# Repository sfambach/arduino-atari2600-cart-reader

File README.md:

# Atari 2600 Cartridge Reader

Arduino firmware for dumping Atari 2600 cartridges, including bankswitched games.

Project page: https://www.fambach.net/ (Retro Projekt – Atari 2600 ROM einlesen)

## Boards

| Board | Address bus | Data bus |
|---|---|---|
| Arduino Mega 2560 | A0-A7 = PA0-PA7, A8-A12 = PC0-PC4 | D0-D7 = PL0-PL7 |
| Arduino Uno / Nano | 2 × 74HC595 on SPI (MOSI D11, SCK D13, latch A2): U1 = A0-A7, U2 = A8-A12 | D0-D7 = D2-D9 |
| Uno / Nano, MCP23017 boards | MCP23017 (I2C 0x20): GPA0-7 = A0-A7, GPB0-4 = A8-A12; `#define ADDR_MCP23017` in `hal.h` | D0-D7 = D2-D9 |

Cartridge slot: pin 23 = switched +5 V (BC327, LOW on D10 for Uno/Nano, D8 for Mega; sense on A0), pins 12 and 24 = GND. Read button on A1; reset button on the Arduino RESET line (Uno and Mega shields).

Boards (THT, KiCad) for Uno, Mega and Nano, plus MCP23017 variants for Uno and Nano: [`hardware/`](hardware/).

## Bankswitching

| Scheme | Size | Status |
|---|---|---|
| 2K, 4K | 2/4 KB | |
| F8, F6, F4 (+SC) | 8/16/32 KB | |
| E0 (Parker Bros.) | 8 KB | |
| E7 (M-Network) | 16 KB | |
| FA (CBS RAM+) | 12 KB | |
| FE (Activision) | 8 KB | experimental |
| 3F (Tigervision) | 8 KB+ (`D 3F <kb>`) | experimental |

Untested on hardware so far.

## Usage

Serial 115200 baud: `L` lists schemes, `D <scheme> [kb]` dumps, `P <hexaddr>` reads one byte, `S` prints the orientation and supply readings. The read button (A1) repeats the last `D` command (4K until one was given); `dump.py <port> listen <prefix>` saves those dumps. The cartridge is powered only during `D`, `P`, `S` and a button read, and only after the orientation check passed (experimental, see [`hardware/`](hardware/)).

```
pip install pyserial
python3 tools/dump.py /dev/ttyACM0 F8 game.bin
```

Test the dump with the emulator [Stella](https://stella-emu.github.io/).

## Credits

- [retrocartdumper](https://github.com/SvOlli/retrocartdumper) by Sven Oliver Moll (GPLv3)
- [Cart Reader](https://github.com/sanni/cartreader) by sanni (GPLv3)
- [vcsreaderfw](https://github.com/keoni29/vcsreaderfw) by Koen van Vliet (MIT)

## Authors

- **Stefan Fambach** (SteFam) – idea and concept, review and testing – https://www.fambach.net
- **Claude** (Anthropic AI) – implementation, via Claude Code

## AI disclosure

This project is built with AI assistance. Stefan Fambach had the idea, wrote the concept and reviews and tests every change; the implementation (schematics, PCB design files, firmware and documentation) is written largely by Claude (Anthropic) via Claude Code.

## License

GPLv3

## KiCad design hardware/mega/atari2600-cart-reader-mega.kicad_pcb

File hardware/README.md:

# Boards

Through-hole (THT) boards that carry the 24-pin cartridge slot. Pinout matches `AtariCartReader/hal.h`. Version 1.2.

| Variant | Board | Size | Notes |
|---|---|---|---|
| [`uno/`](uno/) | Arduino Uno R3 shield | 68.6 × 53.3 mm | address bus via 2 × 74HC595 (SPI) |
| [`mega/`](mega/) | Arduino Mega 2560 shield | 101.6 × 53.3 mm | direct port wiring (PA, PC, PL) |
| [`nano/`](nano/) | carrier for a plugged-in Arduino Nano | 80 × 62 mm | same circuit and firmware as the Uno, 2 × M3 holes |
| [`uno-mcp23017/`](uno-mcp23017/) | Uno shield, alternative | 68.6 × 53.3 mm | address bus via MCP23017 (I²C), firmware with `#define ADDR_MCP23017` in `hal.h` |
| [`nano-mcp23017/`](nano-mcp23017/) | Nano carrier, alternative | 80 × 62 mm | address bus via MCP23017 (I²C), firmware with `#define ADDR_MCP23017` |

Each folder: KiCad 7 project, schematic PDF, Gerber + drill ZIP, render, DRC report (0 errors, 0 unconnected; remaining warnings are silkscreen near the board edge and, on the shields, the modified shield footprint).

Changes in 1.2: Uno and Nano address bus via two 74HC595 on SPI (MOSI D11, SCK D13, latch A2) instead of the MCP23017, which costs about 1.75 € (Reichelt); the MCP23017 boards stay as `-mcp23017` variants. Read button (SW2, A1 to GND) on all boards, reset button (SW1, on the Arduino RESET line) on the Uno and Mega shields (the Nano's own reset button stays reachable), 6 × 6 mm tactile switches; Uno: C1 moved right to make room.

Changes in 1.1: switched cartridge supply with polyfuse and orientation check, mounting holes for the slot flanges (M2.5) as fixing points for the 3D-printed guide, ICSP header removed from the shields (firmware goes over USB), Uno: the mounting hole next to the ICSP header removed, Mega: slot moved to the middle of the board. Silkscreen: each part shows reference and value ("R4 10k"), "fambach.net" in the front title.

## Switched cartridge supply

[`switch/schalter.png`](switch/schalter.png): the cartridge is only powered while the firmware reads it. A BC327 (PNP) switches pin 23, a 200 mA polyfuse limits a short, and A0 measures the switched rail.

- Before switching on, the firmware checks the orientation with the supply off: a weak pull-up on data line D2 back-feeds the cartridge's VCC through the ROM's protection diode only if the cartridge sits the right way round. A reversed cartridge (or none) leaves A0 low and the supply stays off.
- All address lines are held low during the check, so a reversed cartridge's A12 (on slot pin 7 = A1) keeps the ROM disabled.
- The ADC thresholds are not confirmed on hardware yet; the `S` command prints both readings for calibration.

| Signal | Uno / Nano | Mega |
|---|---|---|
| Switch (LOW = on) | D10 | D8 |
| Sense (via 10 kΩ) | A0 | A0 |

## Wiring

| Cartridge pin | Signal | Uno shield / Nano board | Mega shield |
|---|---|---|---|
| 8 … 1 | A0 … A7 | U1 QA … QH (74HC595) | D22 … D29 (PA0 … PA7) |
| 22, 21, 19, 20, 18 | A8, A9, A10, A11, A12 | U2 QA … QE (74HC595) | D37 … D33 (PC0 … PC4) |
| 9, 10, 11, 13 … 17 | D0 … D7 | D2 … D9 | D49 … D42 (PL0 … PL7) |
| 23 | +5 V (switched) | BC327 collector | BC327 collector |
| 12, 24 | GND | GND | GND |

Uno / Nano: U1 SER = MOSI (D11), U1 QH' → U2 SER, SRCLK = SCK (D13), RCLK = latch (A2), OE to GND, SRCLR to +5 V; U2 QF–QH unused. The firmware shifts A8–A12 first, then A0–A7.

MCP23017 variants: MCP23017 at I2C 0x20 (A0–A2 to GND, RESET to +5 V), SDA = A4, SCL = A5 with 4k7 pull-ups; GPA0–7 = A0–A7, GPB0–4 = A8–A12.

## Bill of materials

| Ref | Part | Uno | Mega | Nano |
|---|---|---|---|---|
| J1 | Atari 2600 cartridge slot, 2 × 12, 2.54 mm | 1 | 1 | 1 |
| U1, U2 | 74HC595 (DIP-16) + DIP-16 socket | 2 | – | 2 |
| R3 | 1 kΩ, axial | 1 | 1 | 1 |
| R4, R5 | 10 kΩ, axial | 2 | 2 | 2 |
| R6 | 100 kΩ, axial | 1 | 1 | 1 |
| Q1 | BC327 (PNP, TO-92) | 1 | 1 | 1 |
| F1 | Polyfuse 200 mA radial, 5.08 mm (MF-R020, RXEF020) | 1 | 1 | 1 |
| C1, C2, C4 | 100 nF ceramic, 5 mm pitch | 3 | 1 (C2) | 3 |
| C3 | 10 µF electrolytic, 5 mm, 2 mm pitch | 1 | 1 | 1 |
| SW1, SW2 | Tactile switch 6 × 6 mm THT (SW1 reset, SW2 read) | 2 | 2 | 1 (SW2) |
| – | Stacking headers (Uno: 6, 8, 8, 10; Mega shield set) or 2 × 15 female headers (Nano) | 1 set | 1 set | 2 |
| – | M2.5 screws for the slot flanges / guide | 2 | 2 | 2 |

MCP23017 variants instead of U1/U2 and C4: U1 MCP23017-E/SP (DIP-28) + DIP-28 socket, R1/R2 4.7 kΩ axial, C1 100 nF.

## Assumptions

- **Slot row spacing 5.5 mm** centre to centre, pitch 2.54 mm, flange holes 45.5 mm apart. Footprint: `lib/atari.pretty`.
- **Guide base plate 61 × 17 mm** around the slot (dashed on F.Fab): no other parts there; `generator/plate.py` checks this on every build. The guide itself is not designed yet.
- The pin 13–24 row is the cartridge's label side (silkscreen "Etikettseite").
- Not built or tested yet.

## Cartridge orientation

[`pinout/pinout.png`](pinout/pinout.png) shows the cartridge contacts seen from below with the label up: pins 13–24 (D3 … +5V, GND) are on the label side, pins 1–12 (A7 … GND) on the back. Pin k sits opposite pin 25 − k, so a cartridge inserted the wrong way round puts +5V on D2. Sources: [WiringVCS](https://github.com/drzaiusx11/WiringVCS) and [The Hardware Book](https://isa.umh.es/temas/micros/doc/hwb/co_CartridgeAtari2600.html); quick check: pin 23 has continuity to the ROM's VCC pin.

## Cartridge slot drawing

[`slot-drawing/slot-masse.png`](slot-drawing/slot-masse.png) is a 2D dimension sketch of the 24-pin cartridge slot (top, front, side and bottom views), measured by hand; `zeichnung.py` regenerates it. It is the basis for the planned 3D-printed cartridge guide. A slot from another source may differ, so check these values first:

- Pins 2×12, pitch 2.54 mm, rows 5.5 mm apart (centre to centre).
- Overall length 51.3 mm, width 9 mm, height 16.1 mm above the board (6 mm lower part + 10.1 mm upper part).
- Lower part below the flanges: 35 mm long, 6 mm high, 7.4 mm wide.
- Body between the flanges 36.8 mm. Mounting flanges 7.2 mm long, 7.1 mm wide (across the pin rows), 6.5 mm high, with a Ø2.8 mm hole centred 2.9 mm from the outer edge.
- Flange underside flush with the top of the lower part (6 mm above the board), flange top at 12.5 mm. That leaves 3.6 mm to the slot top (confirmed).
- Card slot opening: 33.3 mm long, 2.2 mm wide; the spring contacts close to about 1.4 mm (estimated), which suits a 1.6 mm cartridge PCB. Slot depth 9 mm.

The measured slot sat on round-pin socket strips for extra height. They are not needed and are left out; the guide sets the cartridge height instead.

## Rebuild

Needs KiCad 7 (pcbnew Python), `xvfb-run`, Java and [Freerouting 1.9.0](https://github.com/freerouting/freerouting) at `/opt/tools/freerouting.jar` (or `FREEROUTING=`).

```
sh generator/build.sh uno|mega|nano     # schematic, board, routing, DRC, guide-plate check
sh generator/outputs.sh uno|mega|nano   # Gerber ZIP, schematic PDF, render
```

`generator/boards.py` holds netlist and placement.

## Credits

Arduino shield symbols and footprints: [arduino-kicad-library](https://github.com/Alarm-Siren/arduino-kicad-library) by Alarm-Siren, CC BY-SA 4.0 (`lib/LICENSE-arduino-library.txt`).

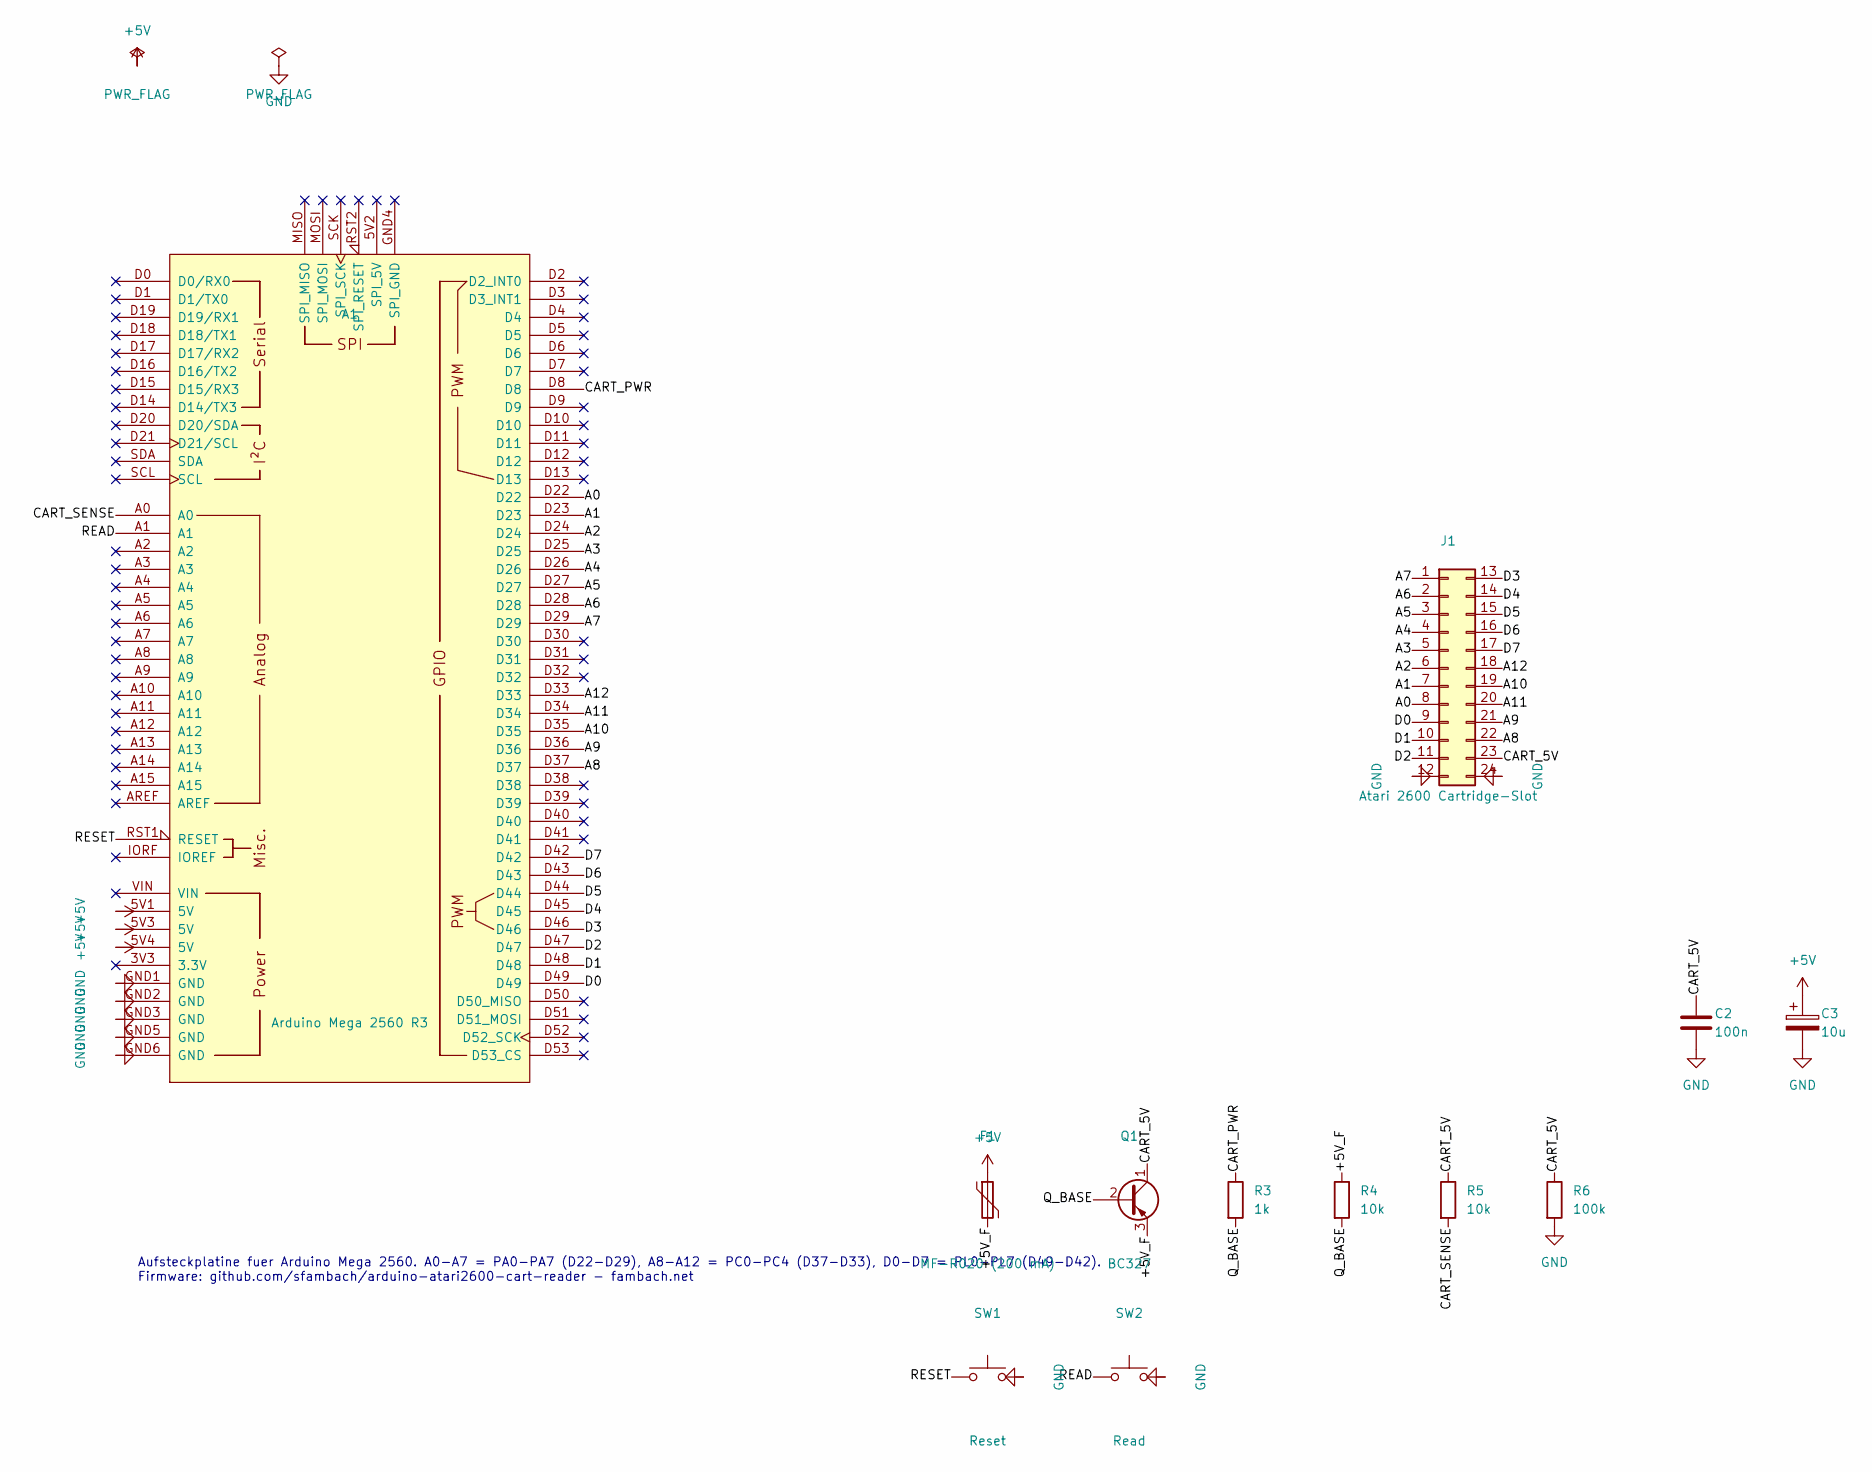
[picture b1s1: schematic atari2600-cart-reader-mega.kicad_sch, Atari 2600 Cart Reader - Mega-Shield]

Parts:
A1: Arduino Mega 2560 R3; Arduino_Mega2560_R3_Shield
C2: 100n; C_Disc_D5.0mm_W2.5mm_P5.00mm
C3: 10u; CP_Radial_D5.0mm_P2.00mm
F1: MF-R020 (200 mA); Fuse_PTC_Radial_P5.08mm
J1: Atari 2600 Cartridge-Slot; Atari2600_Cart_Slot_2x12_P2.54mm_Row5.50mm_Guide
Q1: BC327; TO-92_Inline
R3: 1k; R_Axial_DIN0207_L6.3mm_D2.5mm_P7.62mm_Horizontal
R4, R5: 10k; R_Axial_DIN0207_L6.3mm_D2.5mm_P7.62mm_Horizontal
R6: 100k; R_Axial_DIN0207_L6.3mm_D2.5mm_P7.62mm_Horizontal
SW1: Reset; SW_PUSH_6mm
SW2: Read; SW_PUSH_6mm

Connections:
+5V: A1.5V1 (5V), A1.5V3 (5V), A1.5V4 (5V), C3.1, F1.1
/+5V_F: F1.2, Q1.3 (E), R4.1
/A0: A1.D22, J1.8
/A1: A1.D23, J1.7
/A2: A1.D24, J1.6
/A3: A1.D25, J1.5
/A4: A1.D26, J1.4
/A5: A1.D27, J1.3
/A6: A1.D28, J1.2
/A7: A1.D29, J1.1
/A8: A1.D37, J1.22
/A9: A1.D36, J1.21
/A10: A1.D35, J1.19
/A11: A1.D34, J1.20
/A12: A1.D33, J1.18
/CART_5V: C2.1, J1.23, Q1.1 (C), R5.1, R6.1
/CART_PWR: A1.D8, R3.1
/CART_SENSE: A1.A0, R5.2
/D0: A1.D49, J1.9
/D1: A1.D48, J1.10
/D2: A1.D47, J1.11
/D3: A1.D46, J1.13
/D4: A1.D45, J1.14
/D5: A1.D44, J1.15
/D6: A1.D43, J1.16
/D7: A1.D42, J1.17
/Q_BASE: Q1.2 (B), R3.2, R4.2
/READ: A1.A1, SW2.1
/RESET: A1.RST1 (RESET), SW1.1
GND: A1.GND1 (GND), A1.GND2 (GND), A1.GND3 (GND), A1.GND5 (GND), A1.GND6 (GND), C2.2, C3.2, J1.12, J1.24, R6.2, SW1.2, SW2.2

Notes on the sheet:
Aufsteckplatine fuer Arduino Mega 2560. A0-A7 = PA0-PA7 (D22-D29), A8-A12 = PC0-PC4 (D37-D33), D0-D7 = PL0-PL7 (D49-D42). Firmware: github.com/sfambach/arduino-atari2600-cart-reader - fambach.net

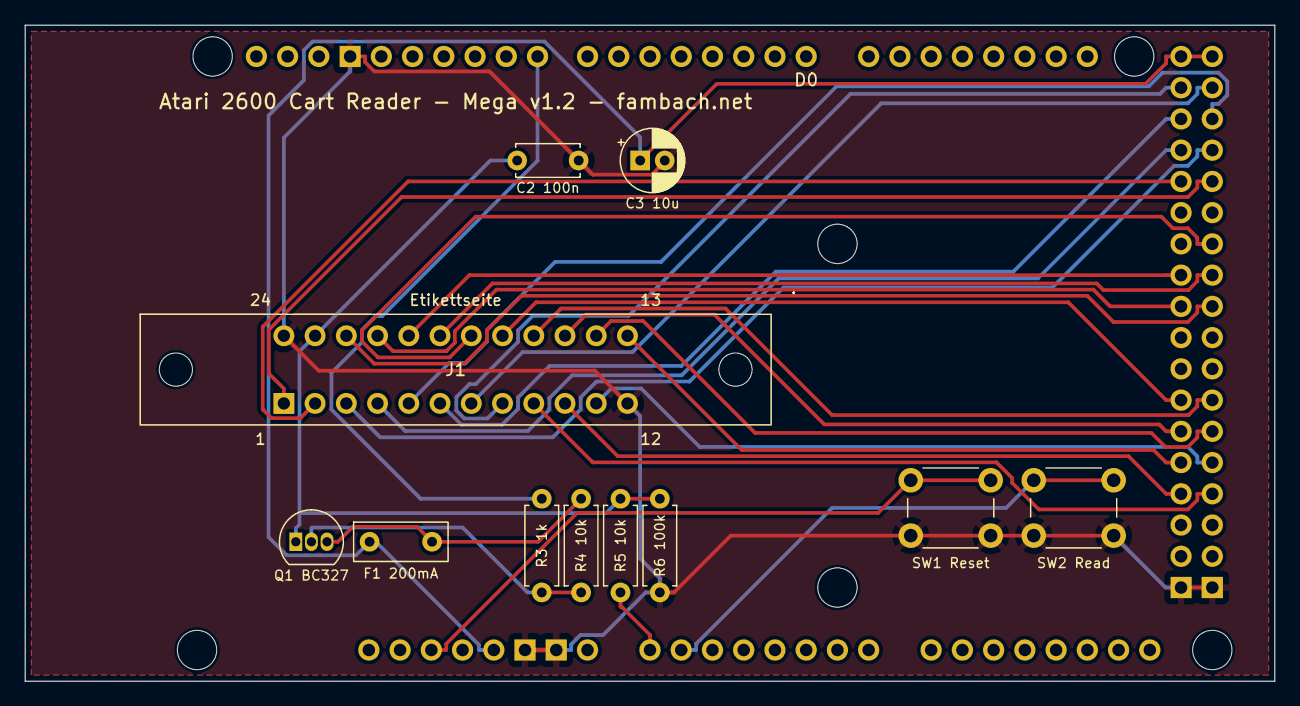
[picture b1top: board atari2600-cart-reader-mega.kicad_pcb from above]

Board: 2 copper layers, 101.6 x 53.3 mm, 12 parts (0 on the bottom side), 30 nets.

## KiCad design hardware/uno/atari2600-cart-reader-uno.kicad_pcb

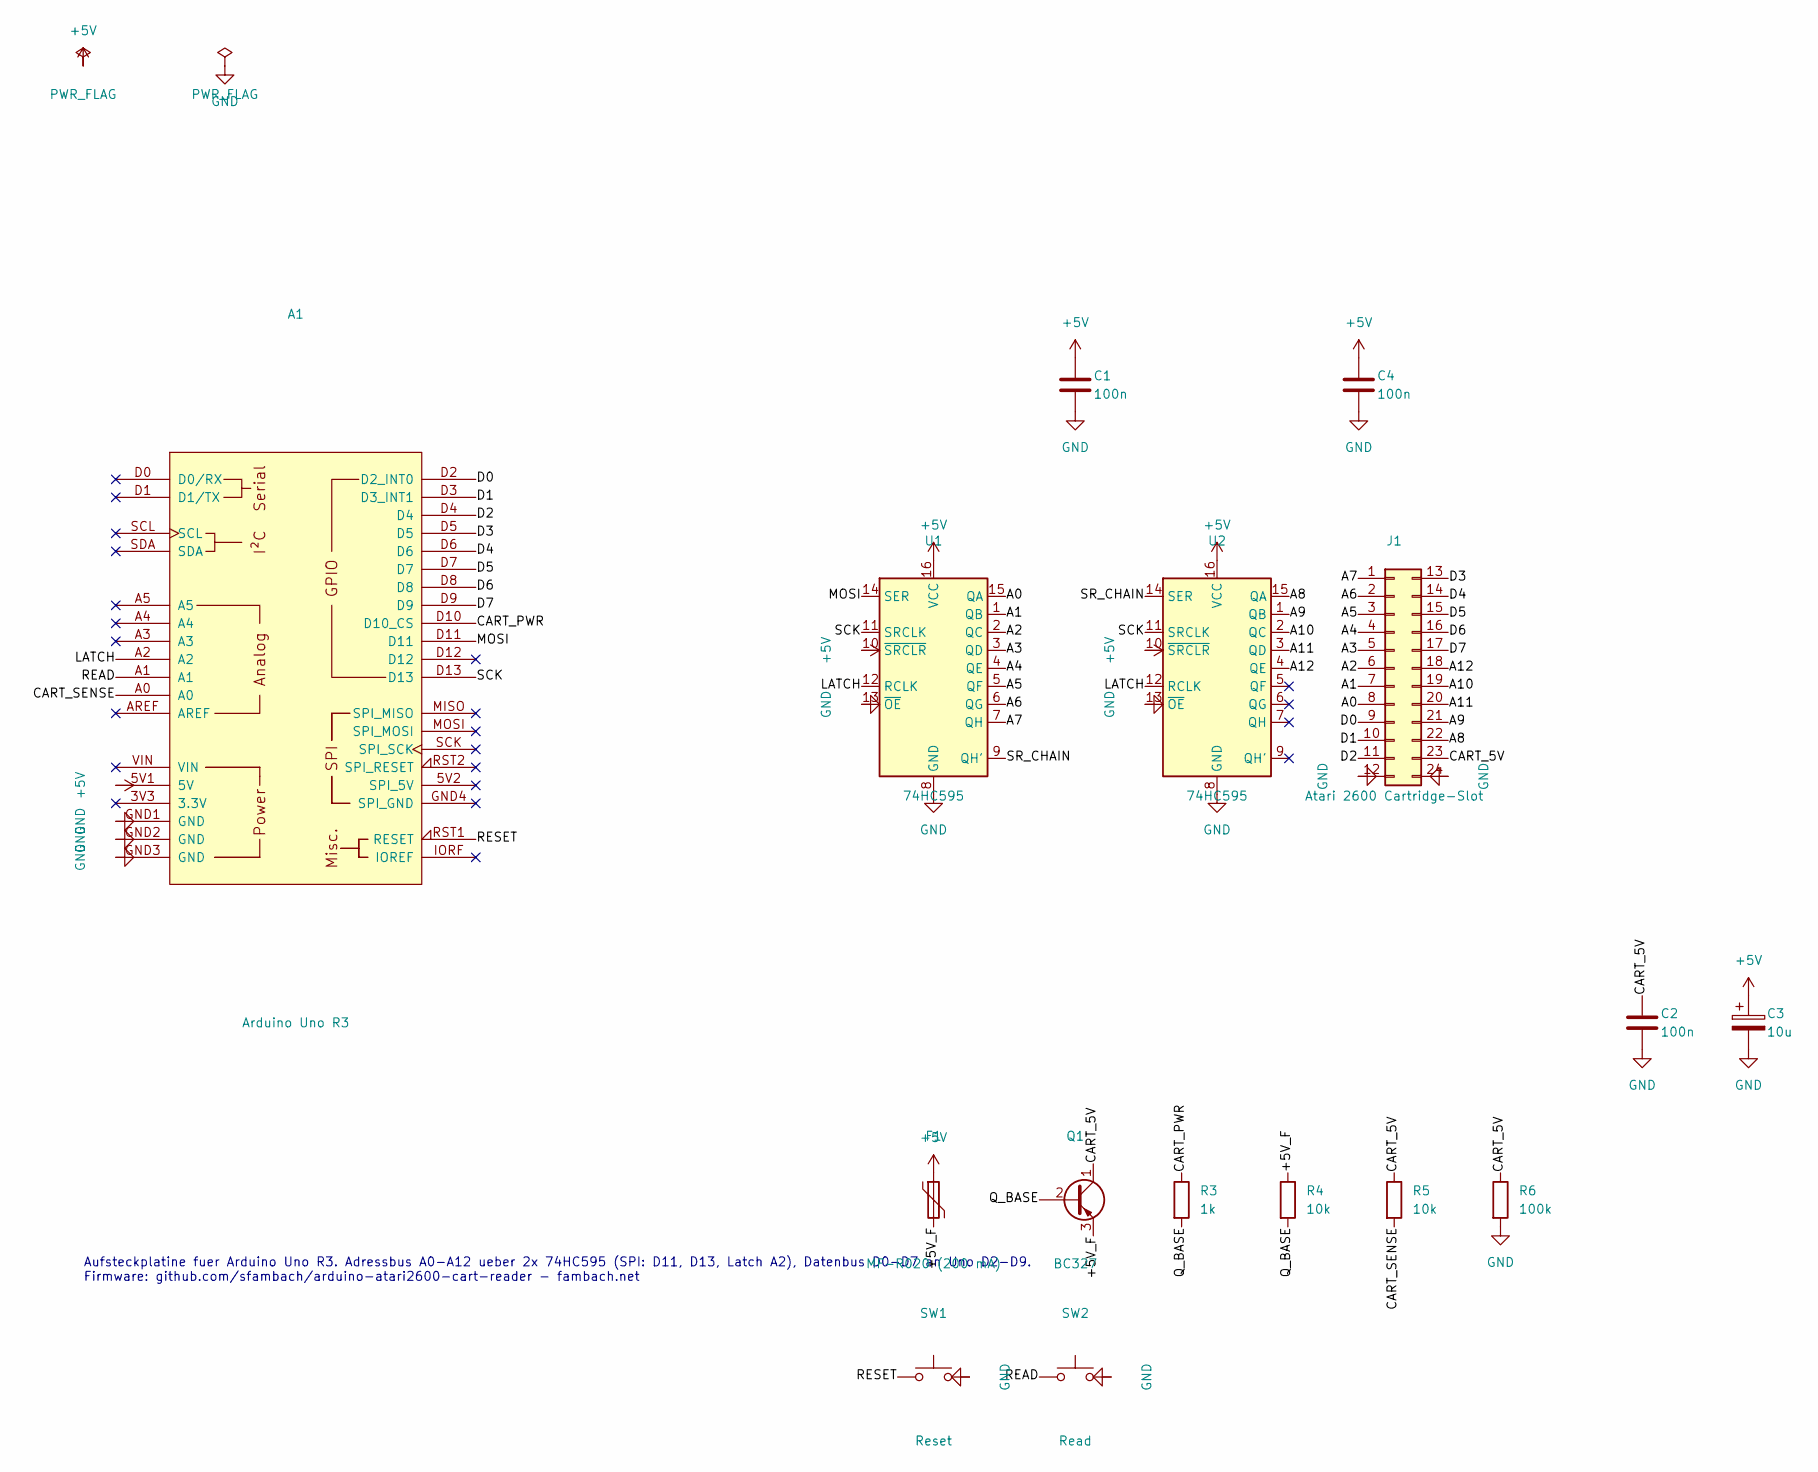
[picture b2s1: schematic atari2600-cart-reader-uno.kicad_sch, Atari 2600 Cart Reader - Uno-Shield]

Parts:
A1: Arduino Uno R3; Arduino_Uno_R3_Shield
C1, C2, C4: 100n; C_Disc_D5.0mm_W2.5mm_P5.00mm
C3: 10u; CP_Radial_D5.0mm_P2.00mm
F1: MF-R020 (200 mA); Fuse_PTC_Radial_P5.08mm
J1: Atari 2600 Cartridge-Slot; Atari2600_Cart_Slot_2x12_P2.54mm_Row5.50mm_Guide
Q1: BC327; TO-92_Inline
R3: 1k; R_Axial_DIN0207_L6.3mm_D2.5mm_P7.62mm_Horizontal
R4, R5: 10k; R_Axial_DIN0207_L6.3mm_D2.5mm_P7.62mm_Horizontal
R6: 100k; R_Axial_DIN0207_L6.3mm_D2.5mm_P7.62mm_Horizontal
SW1: Reset; SW_PUSH_6mm
SW2: Read; SW_PUSH_6mm
U1, U2: 74HC595; DIP-16_W7.62mm_Socket

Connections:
+5V: A1.5V1 (5V), C1.1, C3.1, C4.1, F1.1, U1.10 (~SRCLR), U1.16 (VCC), U2.10 (~SRCLR), U2.16 (VCC)
/+5V_F: F1.2, Q1.3 (E), R4.1
/A0: J1.8, U1.15 (QA)
/A1: J1.7, U1.1 (QB)
/A2: J1.6, U1.2 (QC)
/A3: J1.5, U1.3 (QD)
/A4: J1.4, U1.4 (QE)
/A5: J1.3, U1.5 (QF)
/A6: J1.2, U1.6 (QG)
/A7: J1.1, U1.7 (QH)
/A8: J1.22, U2.15 (QA)
/A9: J1.21, U2.1 (QB)
/A10: J1.19, U2.2 (QC)
/A11: J1.20, U2.3 (QD)
/A12: J1.18, U2.4 (QE)
/CART_5V: C2.1, J1.23, Q1.1 (C), R5.1, R6.1
/CART_PWR: A1.D10 (D10_CS), R3.1
/CART_SENSE: A1.A0, R5.2
/D0: A1.D2 (D2_INT0), J1.9
/D1: A1.D3 (D3_INT1), J1.10
/D2: A1.D4, J1.11
/D3: A1.D5, J1.13
/D4: A1.D6, J1.14
/D5: A1.D7, J1.15
/D6: A1.D8, J1.16
/D7: A1.D9, J1.17
/LATCH: A1.A2, U1.12 (RCLK), U2.12 (RCLK)
/MOSI: A1.D11, U1.14 (SER)
/Q_BASE: Q1.2 (B), R3.2, R4.2
/READ: A1.A1, SW2.1
/RESET: A1.RST1 (RESET), SW1.1
/SCK: A1.D13, U1.11 (SRCLK), U2.11 (SRCLK)
/SR_CHAIN: U1.9 (QH'), U2.14 (SER)
GND: A1.GND1 (GND), A1.GND2 (GND), A1.GND3 (GND), C1.2, C2.2, C3.2, C4.2, J1.12, J1.24, R6.2, SW1.2, SW2.2, U1.8 (GND), U1.13 (~OE), U2.8 (GND), U2.13 (~OE)

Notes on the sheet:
Aufsteckplatine fuer Arduino Uno R3. Adressbus A0-A12 ueber 2x 74HC595 (SPI: D11, D13, Latch A2), Datenbus D0-D7 an Uno D2-D9. Firmware: github.com/sfambach/arduino-atari2600-cart-reader - fambach.net

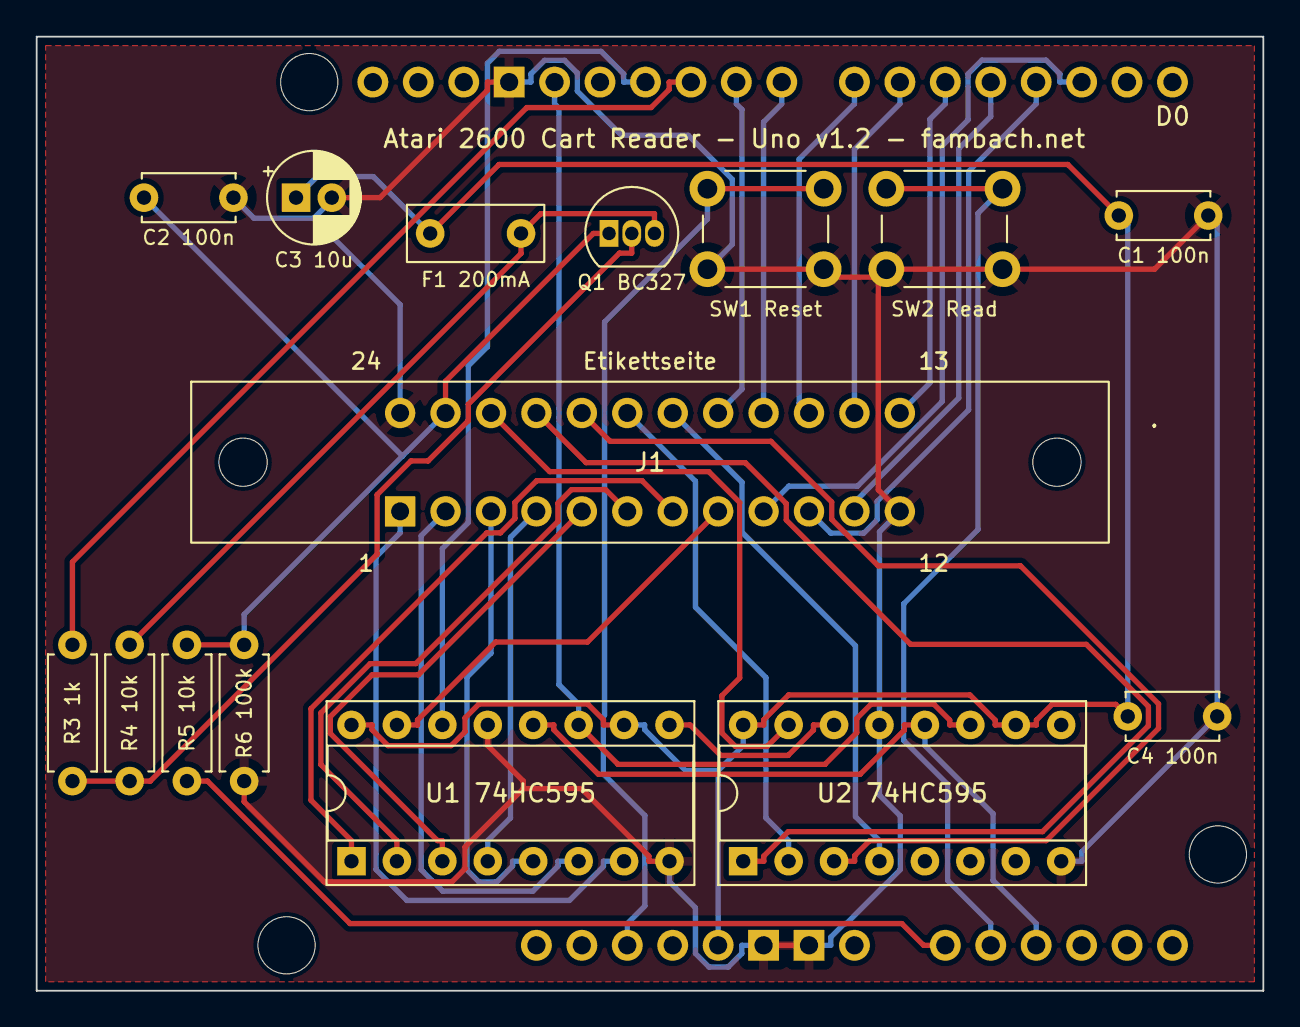
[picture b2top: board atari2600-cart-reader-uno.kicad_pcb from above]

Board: 2 copper layers, 68.6 x 53.3 mm, 16 parts (0 on the bottom side), 34 nets.

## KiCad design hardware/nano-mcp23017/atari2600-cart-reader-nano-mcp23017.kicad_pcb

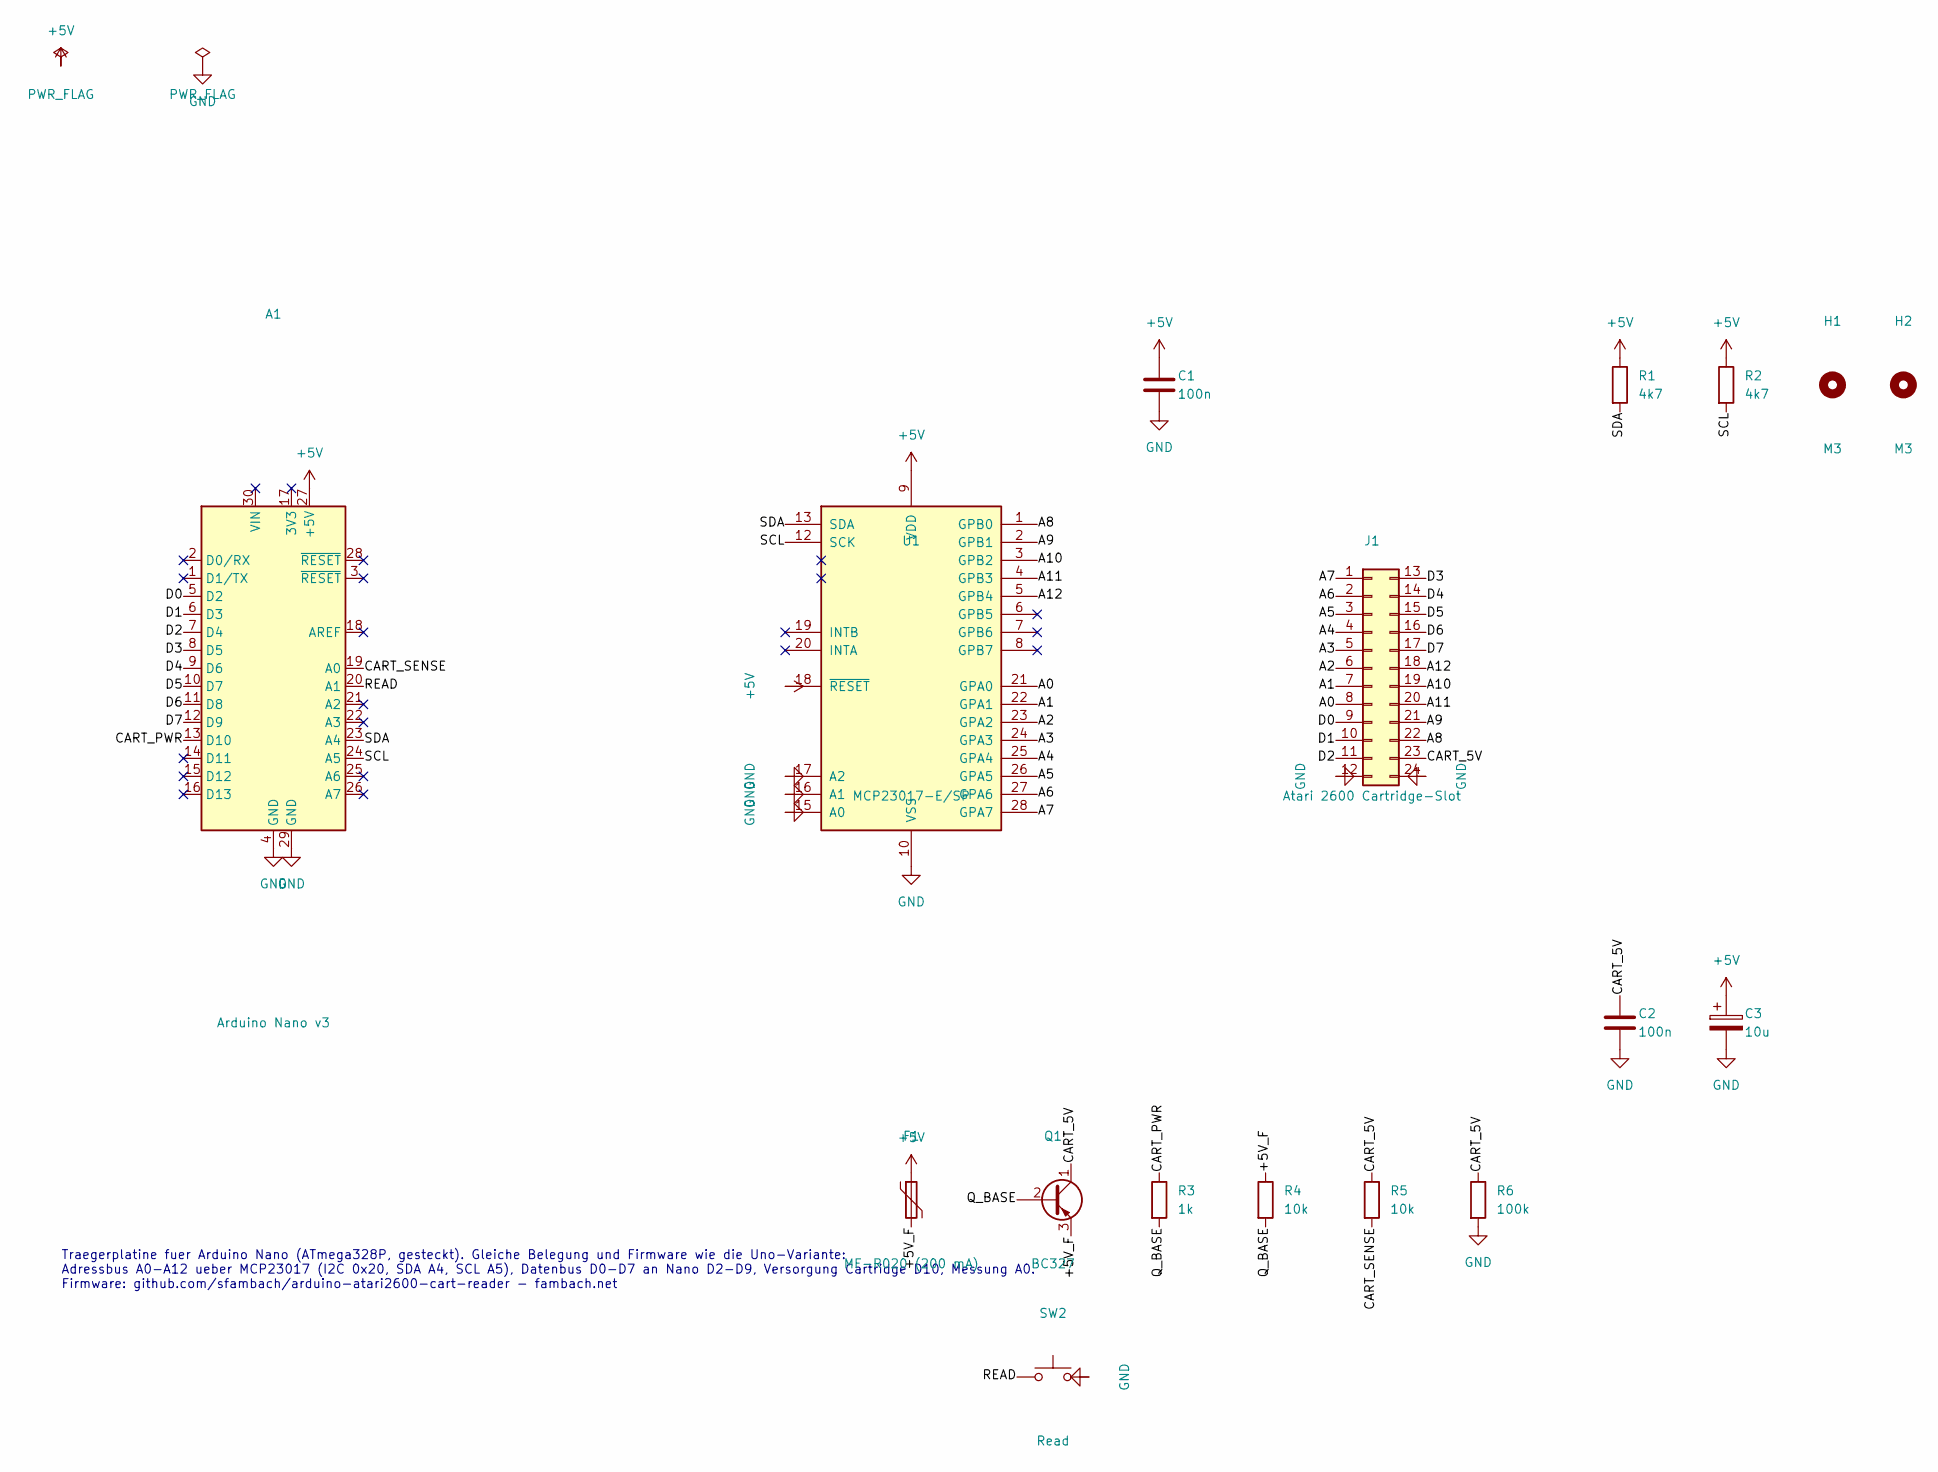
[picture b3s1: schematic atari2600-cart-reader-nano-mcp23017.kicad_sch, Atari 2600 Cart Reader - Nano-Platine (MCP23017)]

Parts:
A1: Arduino Nano v3; Arduino_Nano
C1, C2: 100n; C_Disc_D5.0mm_W2.5mm_P5.00mm
C3: 10u; CP_Radial_D5.0mm_P2.00mm
F1: MF-R020 (200 mA); Fuse_PTC_Radial_P5.08mm
H1, H2: M3; MountingHole_3.2mm_M3
J1: Atari 2600 Cartridge-Slot; Atari2600_Cart_Slot_2x12_P2.54mm_Row5.50mm_Guide
Q1: BC327; TO-92_Inline
R1, R2: 4k7; R_Axial_DIN0207_L6.3mm_D2.5mm_P7.62mm_Horizontal
R3: 1k; R_Axial_DIN0207_L6.3mm_D2.5mm_P7.62mm_Horizontal
R4, R5: 10k; R_Axial_DIN0207_L6.3mm_D2.5mm_P7.62mm_Horizontal
R6: 100k; R_Axial_DIN0207_L6.3mm_D2.5mm_P7.62mm_Horizontal
SW2: Read; SW_PUSH_6mm
U1: MCP23017-E/SP; DIP-28_W7.62mm_Socket

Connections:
+5V: A1.27 (+5V), C1.1, C3.1, F1.1, R1.1, R2.1, U1.9 (VDD), U1.18 (~RESET)
/+5V_F: F1.2, Q1.3 (E), R4.1
/A0: J1.8, U1.21 (GPA0)
/A1: J1.7, U1.22 (GPA1)
/A2: J1.6, U1.23 (GPA2)
/A3: J1.5, U1.24 (GPA3)
/A4: J1.4, U1.25 (GPA4)
/A5: J1.3, U1.26 (GPA5)
/A6: J1.2, U1.27 (GPA6)
/A7: J1.1, U1.28 (GPA7)
/A8: J1.22, U1.1 (GPB0)
/A9: J1.21, U1.2 (GPB1)
/A10: J1.19, U1.3 (GPB2)
/A11: J1.20, U1.4 (GPB3)
/A12: J1.18, U1.5 (GPB4)
/CART_5V: C2.1, J1.23, Q1.1 (C), R5.1, R6.1
/CART_PWR: A1.13 (D10), R3.1
/CART_SENSE: A1.19 (A0), R5.2
/D0: A1.5 (D2), J1.9
/D1: A1.6 (D3), J1.10
/D2: A1.7 (D4), J1.11
/D3: A1.8 (D5), J1.13
/D4: A1.9 (D6), J1.14
/D5: A1.10 (D7), J1.15
/D6: A1.11 (D8), J1.16
/D7: A1.12 (D9), J1.17
/Q_BASE: Q1.2 (B), R3.2, R4.2
/READ: A1.20 (A1), SW2.1
/SCL: A1.24 (A5), R2.2, U1.12 (SCK)
/SDA: A1.23 (A4), R1.2, U1.13 (SDA)
GND: A1.4 (GND), A1.29 (GND), C1.2, C2.2, C3.2, J1.12, J1.24, R6.2, SW2.2, U1.10 (VSS), U1.15 (A0), U1.16 (A1), U1.17 (A2)

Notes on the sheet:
Traegerplatine fuer Arduino Nano (ATmega328P, gesteckt). Gleiche Belegung und Firmware wie die Uno-Variante: Adressbus A0-A12 ueber MCP23017 (I2C 0x20, SDA A4, SCL A5), Datenbus D0-D7 an Nano D2-D9, Versorgung Cartridge D10, Messung A0. Firmware: github.com/sfambach/arduino-atari2600-cart-reader - 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

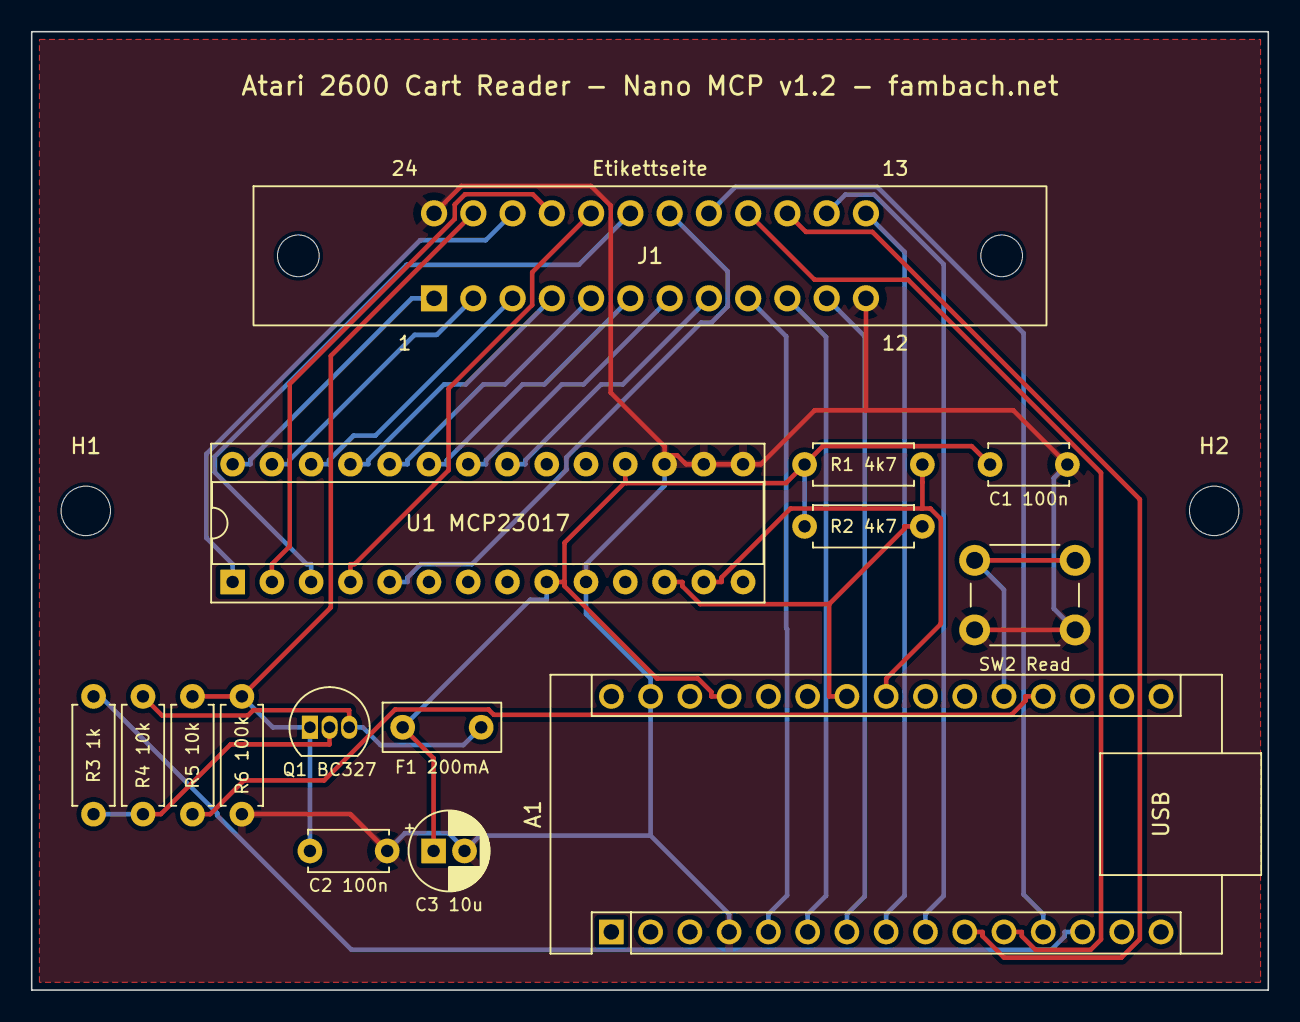
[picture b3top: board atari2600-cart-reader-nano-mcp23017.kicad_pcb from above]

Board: 2 copper layers, 80.0 x 62.0 mm, 17 parts (0 on the bottom side), 31 nets.
